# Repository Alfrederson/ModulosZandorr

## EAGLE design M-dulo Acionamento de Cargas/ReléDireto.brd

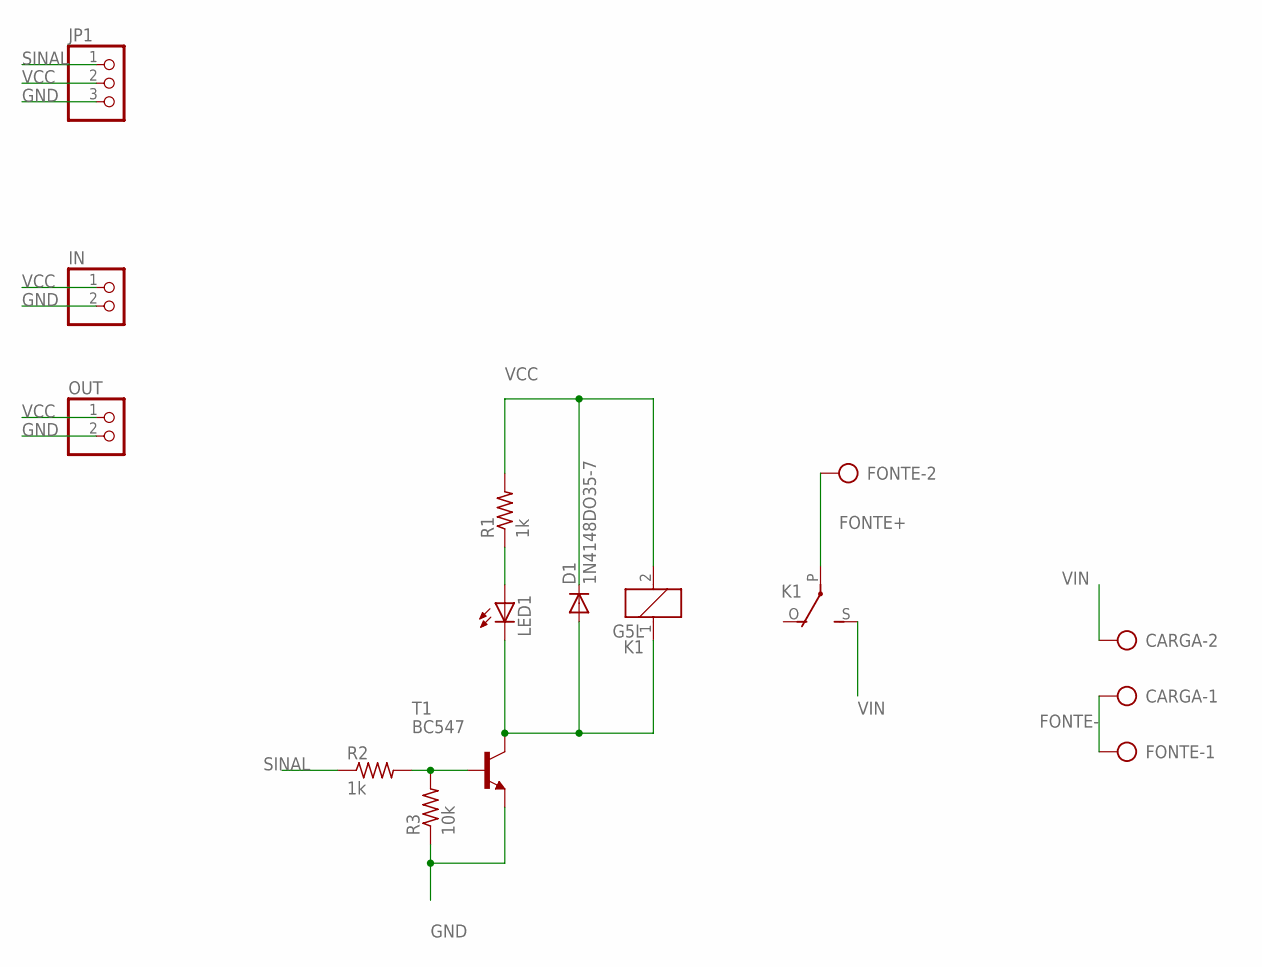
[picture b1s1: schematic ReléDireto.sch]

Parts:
CARGA: AK500/2
D1: 1N4148DO35-7; DO35-7
FONTE: AK500/2
IN: PINHD-1X2; 1X02
JP1: PINHD-1X3; 1X03
K1: G5L; G5LE
LED1: LED5MM
OUT: PINHD-1X2; 1X02
R1, R2: 1k; 0207/7
R3: 10k; 0207/7
T1: BC547; TO92

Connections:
FONTE+: FONTE.2, K1.P
FONTE-: CARGA.1, FONTE.1
GND: IN.2, JP1.3, OUT.2, R3.1, T1.1 (E)
unnamed: LED1.A, R1.1
unnamed: D1.A, K1.1, LED1.K (C), T1.3 (C)
unnamed: R2.2, R3.2, T1.2 (B)
SINAL: JP1.1, R2.1
VCC: D1.C, IN.1, JP1.2, K1.2, OUT.1, R1.2
VIN: CARGA.2, K1.S

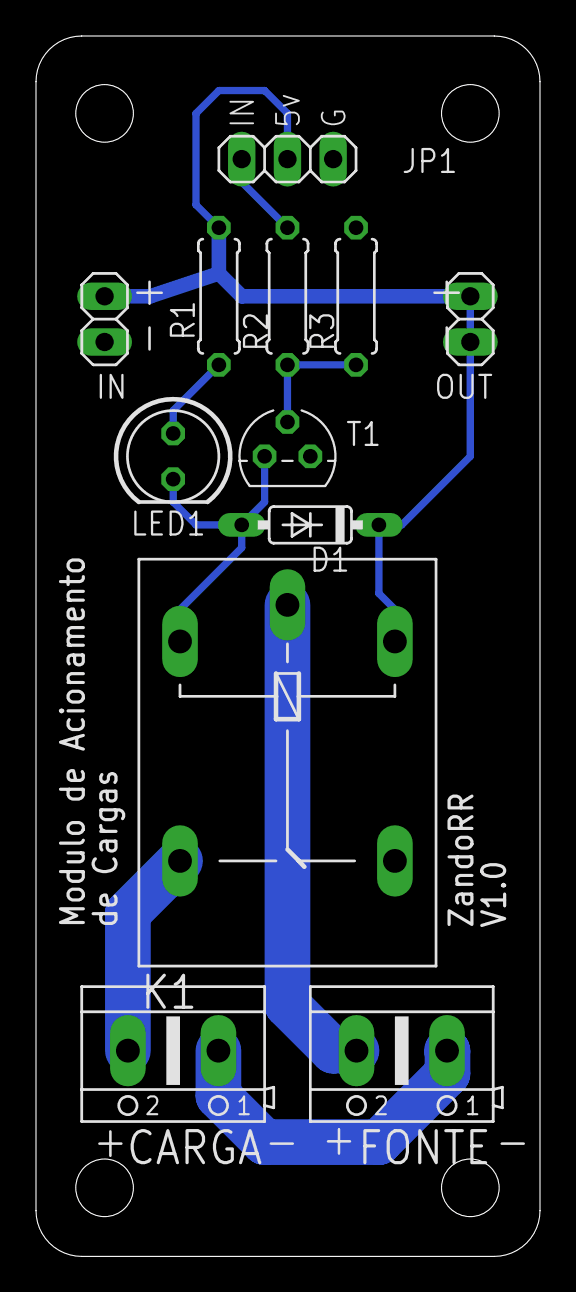
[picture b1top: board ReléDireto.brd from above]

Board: 2 copper layers, 28.0 x 67.8 mm, 12 parts (0 on the bottom side), 9 nets.

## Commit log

2022-07-05 Create Descrição
